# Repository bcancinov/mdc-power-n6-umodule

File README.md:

# mdc-power-n6-umodule
Modular Detector Controller Power -6V uModule Mezzanine Module

## Overview
12V input to -6V output DC-DC module, 3A nominal output, used as one of the `mdc-power-*` bias rails.
Designed for 2 MHz sync operation.
Mezzanine module.

## Power Stage
- Controller: `LTM4651` (uModule)
  - Integrated µModule regulator including controller, MOSFETs, inductor, and support components.
  - EN55022B compliant regulator family (meets Class B EMI limits for conducted and radiated emissions).
  - External sync capability.

## Files
- Schematic: `power_n6_umodule.pdf`

## Board Dimensions
- 44.8 mm x 41.5 mm

## Board Stackup
- 4-layer PCB

## CAD
- Designed using KiCad 9.

## Interface
- Control pins: `EN` (enable) and `PG` / `~PGOOD` (power good).
- Connector: `LSHM-140-04.0-L-DV-A-N-K-TR` (Samtec LSHM series) mezzanine for power and control signals.
  - Common pinout is shared across the 16V, -16V, 6V, and 3.3V variants.
  - Unused output rails are tied to GND on the specific module variant.

## Images
Layout:

3D view:

## License

This hardware design is licensed under the **Creative Commons Attribution-NonCommercial-ShareAlike 4.0 International License** (CC BY-NC-SA 4.0).

You are free to download, modify, and build upon this design for your own research or personal use, provided you give appropriate credit and share your modifications under the exact same license. **Commercial manufacturing or use of these designs is strictly prohibited without explicit permission.**

To view a copy of this license, visit [http://creativecommons.org/licenses/by-nc-sa/4.0/](http://creativecommons.org/licenses/by-nc-sa/4.0/) or see the `LICENSE` file in this repository.

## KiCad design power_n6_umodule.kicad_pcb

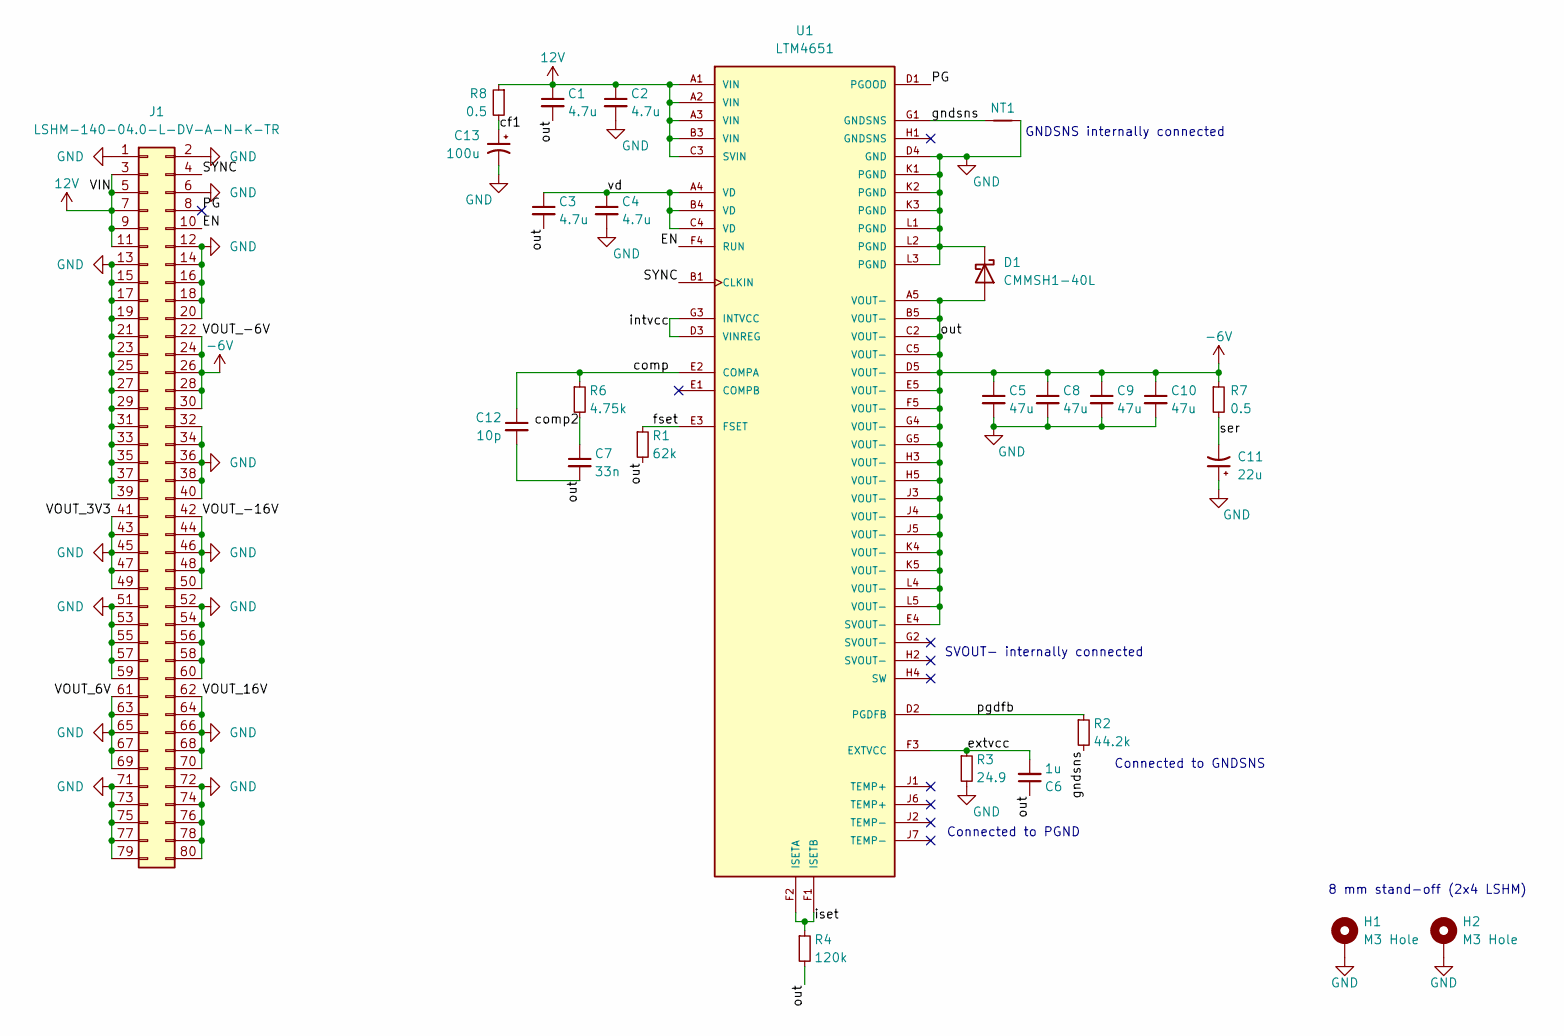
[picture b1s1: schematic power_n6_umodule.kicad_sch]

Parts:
C1, C2, C3, C4: 4.7u; C_1210_3225Metric; MPN GRM32ER71K475KE14L
C5, C8, C9, C10: 47u; C_1210_3225Metric; MPN TMK325ABJ476MM-P
C6: 1u; C_0805_2012Metric; MPN GCM21BR71H105KA03L
C7: 33n; C_1206_3216Metric; MPN GCM3195C1H333JA16D
C11: 22u; CP_EIA-7343-20_Kemet-V; MPN T521V226M025ATE040
C12: 10p; C_0603_1608Metric; MPN GCM1885C2A100FA16D
C13: 100u; T521X; MPN T521X107M025ATE060
D1: CMMSH1-40L; D_SOD-123F; MPN CMMSH1-40L TR PBFREE
H1, H2: M3 Hole; MountingHole_3.2mm_M3_Pad_Via
J1: LSHM-140-04.0-L-DV-A-N-K-TR; SAMTEC_LSHM-140-04.0-L-DV-A-N-K-TR; MPN LSHM-140-04.0-L-DV-A-N-K-TR
NT1: NetTie-2_SMD_Pad0.5mm
R1: 62k; R_0402_1005Metric; MPN CRCW040262K0FKED
R2: 44.2k; R_0402_1005Metric; MPN CRCW040244K2FKED
R3: 24.9; R_0402_1005Metric; MPN CRCW040224R9FKEDHP
R4: 120k; R_0402_1005Metric; MPN MCS04020C1203FE000
R6: 4.75k; R_0402_1005Metric; MPN CRCW04024K75FKED
R7, R8: 0.5; R_0603_1608Metric; MPN RCWE0603R500FKEA
U1: LTM4651; MPN LTM4651EY#PBF

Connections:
12V: C1.1, C2.1, J1.3, J1.5, J1.7, J1.9, J1.11, R8.1, U1.A1 (VIN), U1.A2 (VIN), U1.A3 (VIN), U1.B3 (VIN), U1.C3 (SVIN)
-6V: C1.2, C3.2, C5.1, C6.1, C7.2, C8.1, C9.1, C10.1, C12.2, D1.2 (A), J1.22, J1.24, J1.26, J1.28, J1.30, R1.2, R4.2, R7.1, U1.A5 (VOUT-), U1.B5 (VOUT-), U1.C2 (VOUT-), U1.C5 (VOUT-), U1.D5 (VOUT-), U1.E4 (SVOUT-), U1.E5 (VOUT-), U1.F5 (VOUT-), U1.G4 (VOUT-), U1.G5 (VOUT-), U1.H3 (VOUT-), U1.H5 (VOUT-), U1.J3 (VOUT-), U1.J4 (VOUT-), U1.J5 (VOUT-), U1.K4 (VOUT-), U1.K5 (VOUT-), U1.L4 (VOUT-), U1.L5 (VOUT-)
/EN: J1.10, U1.F4 (RUN)
/PG: J1.8, U1.D1 (PGOOD)
/SYNC: J1.4, U1.B1 (CLKIN)
/cf1: C13.1, R8.2
/comp: C12.1, R6.1, U1.E2 (COMPA)
/comp2: C7.1, R6.2
/extvcc: C6.2, R3.1, U1.F3 (EXTVCC)
/fset: R1.1, U1.E3 (FSET)
/gndsns: NT1.1, R2.2, U1.G1 (GNDSNS)
/intvcc: U1.D3 (VINREG), U1.G3 (INTVCC)
/iset: R4.1, U1.F1 (ISETB), U1.F2 (ISETA)
/pgdfb: R2.1, U1.D2 (PGDFB)
/ser: C11.2, R7.2
/vd: C3.1, C4.1, U1.A4 (VD), U1.B4 (VD), U1.C4 (VD)
GND: C2.2, C4.2, C5.2, C8.2, C9.2, C10.2, C11.1, C13.2, D1.1 (K), H1.1, H2.1, J1.1, J1.2, J1.6, J1.12, J1.13, J1.14, J1.15, J1.16, J1.17, J1.18, J1.19, J1.20, J1.21, J1.23, J1.25, J1.27, J1.29, J1.31, J1.32, J1.33, J1.34, J1.35, J1.36, J1.37, J1.38, J1.39, J1.40, J1.41, J1.42, J1.43, J1.44, J1.45, J1.46, J1.47, J1.48, J1.49, J1.50, J1.51, J1.52, J1.53, J1.54, J1.55, J1.56, J1.57, J1.58, J1.59, J1.60, J1.61, J1.62, J1.63, J1.64, J1.65, J1.66, J1.67, J1.68, J1.69, J1.70, J1.71, J1.72, J1.73, J1.74, J1.75, J1.76, J1.77, J1.78, J1.79, J1.80, NT1.2, R3.2, U1.D4 (GND), U1.K1 (PGND), U1.K2 (PGND), U1.K3 (PGND), U1.L1 (PGND), U1.L2 (PGND), U1.L3 (PGND)

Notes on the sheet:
SVOUT- internally connected
8 mm stand-off (2x4 LSHM)
Connected to GNDSNS
GNDSNS internally connected
Connected to PGND

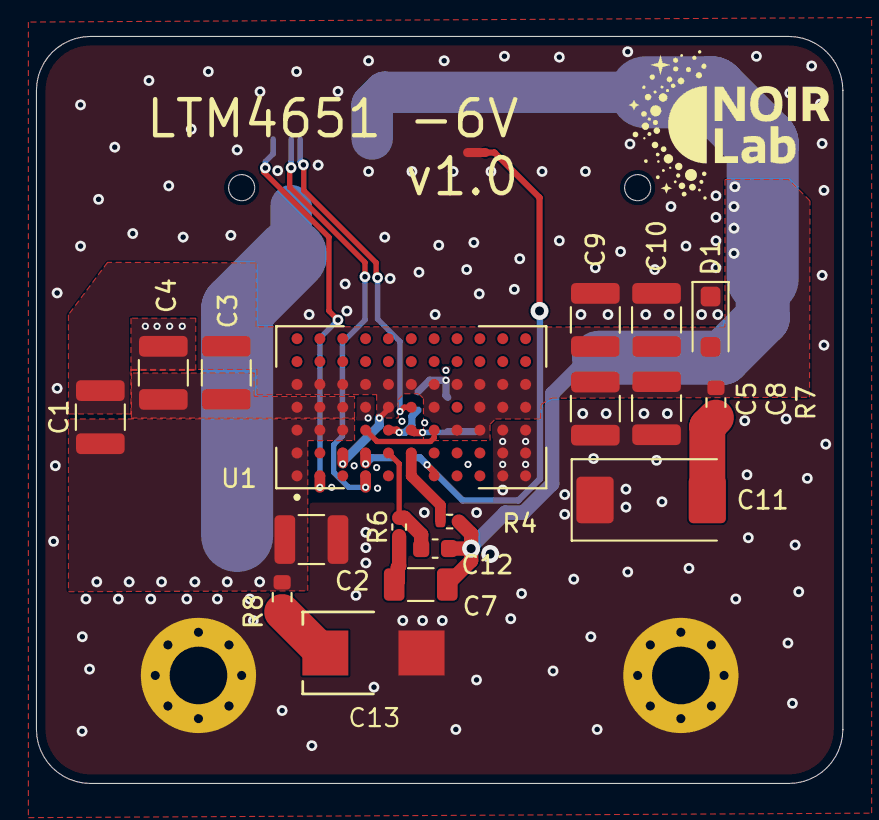
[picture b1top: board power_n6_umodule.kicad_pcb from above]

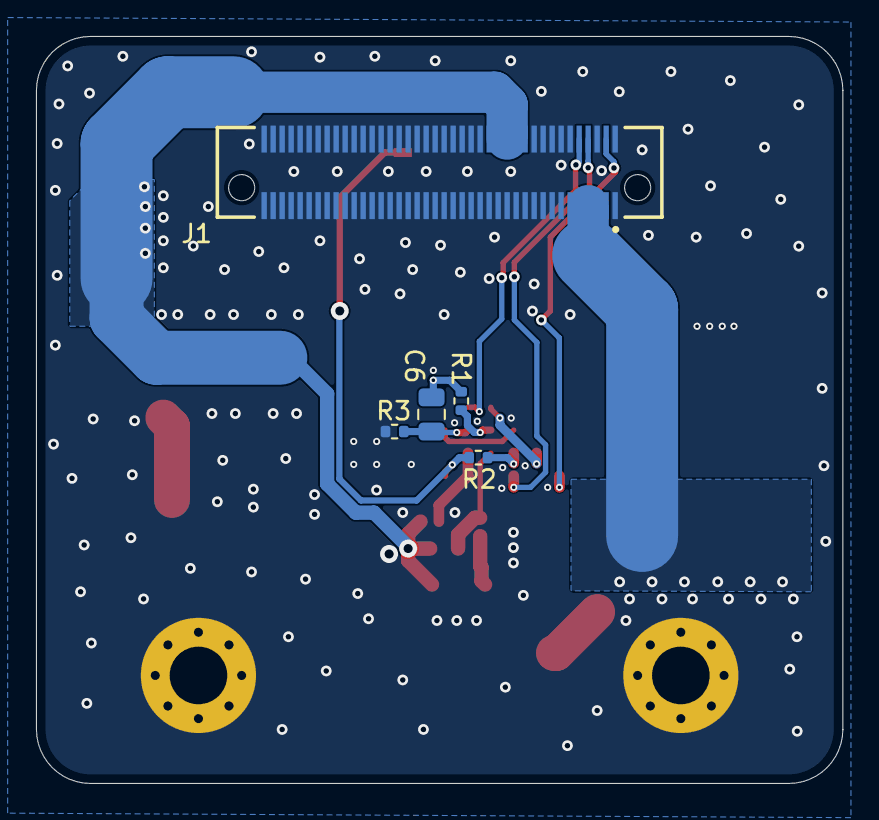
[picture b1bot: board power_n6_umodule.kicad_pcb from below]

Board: 4 copper layers, 44.8 x 41.5 mm, 26 parts (5 on the bottom side), 17 nets.

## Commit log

2026-03-27 add license
